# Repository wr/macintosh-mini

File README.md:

<h1 align="center"> Macintosh Mini</h1>

<p align="center">
  <strong>Turn a Maclock alarm clock into a working Mac with a Raspberry Pi</strong>
</p>

<p align="center">
  <a href="https://wells.ee/projects/macintosh-mini/?ref=gh-macintosh-mini">Build guide</a> ⬪
  <a href="#step-2-install-the-software">Install the software</a> ⬪
  <a href="https://shop.wells.ee/products/macintosh-mini/?ref=gh-macintosh-mini">Buy a kit</a> ⬪
  <a href="#donate">Donate</a>
</p>

<p align="center">
  
  <br />
  <a href="https://www.youtube.com/watch?v=zAbAf5-H5Yo">⏵ Watch the full build on YouTube</a>
</p>

---

## What is it?

A [Maclock](https://www.aliexpress.us/w/wholesale-maclock.html) is a cheap alarm clock built into a shockingly accurate miniature Macintosh shell. This project guts one and rebuilds it around a Raspberry Pi Zero running a 68k or PowerPC emulator, so the tiny Mac actually boots System 7, plays the startup chime, and runs vintage software. Buttons, brightness, sound, Wi-Fi, Bluetooth, and battery all work.

## Step 1: Build or buy one

The [build guide](https://wells.ee/projects/macintosh-mini/?ref=gh-macintosh-mini), on my site, covers everything from opening the clock to the first boot: parts, assembly, software, and troubleshooting.

You can [buy a DIY kit or a finished build](https://shop.wells.ee/products/macintosh-mini/?ref=gh-macintosh-mini) from my maker shop. Faster than shipping from China, and your purchase supports the continued development of this project.

## Step 2: Install the software

**You will need:**
- A Mac ROM file (`064DC91D` is a common one to search for)
- A Mac OS disk image with System 7.0 to 8.5. The [BlueSCSI image library](https://bluescsi.com/docs/BlueSCSI-Images) has ready-made ones, or skip it: the installer offers [our Mac OS 8.1 disk](https://archive.org/details/macos-8.1-basilisk-ii)

**Prepare the MicroSD card**
1. Flash **Raspberry Pi OS Lite (64-bit)** to a microSD card with [Raspberry Pi Imager](https://www.raspberrypi.com/software/). Set your Wi-Fi network and turn on SSH in its settings.
2. Rename your Mac ROM file to `ROM`, and copy it and your disk image, if you have one, to the Pi's home folder:

   ```bash
   scp ROM yourdisk.hda <user>@<pi_ip>:~/
   ```

3. SSH into the Pi and run the install script. It asks a few questions, like which startup chime to play, then does the rest:

   ```bash
   curl -fsSL https://raw.githubusercontent.com/wr/macintosh-mini/main/setup.sh | bash
   ```

The Pi automatically restarts into Mac OS when it's done.

You can run the same command again to install future updates.

* * *

_Optional:_ If you want to skip the automatic script and install everything yourself, or see exactly what the script changes:

- [Set up the Pi](maclock-build/): display, audio, brightness dial and buttons.
-  [Install the emulator](emulators/): Basilisk II or SheepShaver.

## Getting help

Ask in the help forum on [Wells Workshop on Discord](https://discord.gg/gACNgfyB7k), where other builders can help too. Found a bug or want a feature? Open a [GitHub issue](https://github.com/wr/macintosh-mini/issues).

## Credits

Startup chimes and crash sounds are mirrored from D. Schaub's Apple Sounds collection at <https://froods.ca/~dschaub/sound.html>. All sounds are © Apple, Inc.

## Donate

While this project is free and open source, donations are deeply appreciated, and make ongoing development and support possible.
[Donate now](https://www.buymeacoffee.com/wellsworkshop)

## License

Copyright © 2026 Wells Riley.

- **Hardware** (the boards, the bezel and the USB port jig): [CERN-OHL-S-2.0](./LICENSES/CERN-OHL-S-2.0.txt)
- **Software** ([`setup.sh`](./setup.sh) and [`maclock-build/`](./maclock-build/)): [GPL-3.0-or-later](./LICENSES/GPL-3.0-or-later.txt)
- **Everything else** (docs, drawings, photos): [CC BY-SA 4.0](./LICENSES/CC-BY-SA-4.0.txt)

The [Mac chimes](./emulators/chimes/) are Apple's and the display overlay is Waveshare's; neither is covered. [`REUSE.toml`](./REUSE.toml) maps every file.

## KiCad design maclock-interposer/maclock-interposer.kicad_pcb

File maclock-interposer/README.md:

# Macintosh Mini GPIO interposer

A 64.6 × 27.4 mm, 2-layer, 0.8 mm thick KiCad 10 board that sits between the Raspberry Pi (a Zero 2 W or a 3 A+) and the Waveshare 2.8" DPI display. Order it fully assembled — no soldering, and no bent, cut, or desoldered pins on the Pi.

Current revision: 2027.01, for the rev 2027.01 [main board](../maclock-pcb/). **It hasn't been built or tested yet, and the Pi software for it isn't written.** The two revisions don't mix, because their link pins differ: with a rev 2026.11 main board, use the 2026.11 interposer at commit [`e557f70`](https://github.com/wr/macintosh-mini/tree/e557f70d8a1d978d0e488f638d03199df252ab32/maclock-interposer).

An SMD pin header on top plugs into the display and an SMD socket underneath plugs onto the Pi. The socket sits 6 mm lower than the header, so a Pi 3 A+ (65 × 56 mm) clears the handle at the top of the Maclock's rear shell. 35 pins run from one to the other, one via each. Header pins 13, 19, 23, 35 and 37 connect to the Pi side **only** and never reach the display. Four of them, plus 5V and GND, come out on a straight 1×8 female socket (J2) on the screen side at the GPIO 21 end. J2 plugs straight onto the main board's `Link` header, pin 1 onto pin 1, so its pin 1 (SDA) sits at the end away from GPIO 21. A straight 8-way male-to-female Dupont cable works too. Pin 37 (GPIO 26) is unused.

The display uses the Pi's hardware I²C pins for its sync signals, so the Pi reaches the main board's input chip and battery gauge over a software I²C bus on GPIO 10 and 11. Three resistors on the Pi side complete the link. R1 and R2 pull SDA and SCL up to the Pi's 3.3 V. R3 pulls up INT, which the main board's input chip only ever pulls low. The main board has none of these, because the ESP32-P4 build brings its own. The Pi's own pull-up or pull-down on GPIO 10, 11 and 27 should be switched off in software.

The board is drawn the way it sits in the Maclock: Pi mounted upside-down, seen from the screen. Order it **0.8 mm thick**, with **red solder mask and white silkscreen** like the 2027.01 main board, so it can't be paired with a blue 2026.11 board by mistake. The screen side is inverted (silk is the background; the lettering, the open-hardware logo and the character are bare mask). Branding is on the Pi side, and J2's pin labels are on both sides.

| J2 pin | Silk | Net   | Pi header pin | GPIO |
| ------ | ---- | ----- | ------------- | ---- |
| 1      | SDA  | SDA   | 19            | 10   |
| 2      | SCL  | SCL   | 23            | 11   |
| 3      | GND  | GND   | all GNDs      | —    |
| 4      | 5V   | 5V    | 2, 4          | —    |
| 5      | 5V   | 5V    | 2, 4          | —    |
| 6      | GND  | GND   | all GNDs      | —    |
| 7      | INT  | INT   | 13            | 27   |
| 8      | AUD  | AUDIO | 35            | 19   |

## Bill of materials

| Ref | Qty | Part                                                                  | LCSC                                                                  | Notes                                             |
| --- | --- | --------------------------------------------------------------------- | --------------------------------------------------------------------- | ------------------------------------------------- |
| J1  | 1   | 2×20 female socket, 2.54 mm, SMD, 7.1 mm, two locating pegs — Liansheng `FH-00148` | [`C2685092`](https://www.lcsc.com/product-detail/C2685092.html) | **Bottom** side, plugs onto the Pi. LCSC had 3,698 in stock on 2026-11-28 |
| J3  | 1   | 2×20 pin header, 2.54 mm, SMD — Hanbo `HB-PH9-254220PB2GOP`            | [`C6332245`](https://www.lcsc.com/product-detail/C6332245.html)       | Top side, plugs into the display                  |
| J2  | 1   | 1×8 female header (socket), 2.54 mm, 7.1 mm, THT — XFCN `PM254V-11-08-H71-U` | [`C55218707`](https://www.lcsc.com/product-detail/C55218707.html) | Top (screen) side. LCSC had 190 in stock on 2026-11-27 |
| R1, R2 | 2 | 2.2 kΩ ±1% 0402 — UNI-ROYAL `0402WGF2201TCE`                          | [`C25879`](https://www.lcsc.com/product-detail/C25879.html)           | Bottom side. I²C pull-ups on SDA and SCL          |
| R3  | 1   | 10 kΩ ±1% 0402 — UNI-ROYAL `0402WGF1002TCE`                            | [`C25744`](https://www.lcsc.com/product-detail/C25744.html)           | Bottom side. Pull-up on INT                       |

Both sides carry parts, so order two-sided assembly. J1's locating pegs are 1.4 mm long, so on a 0.8 mm board they stick out of the screen side beside J3: ask for the screen side (J3) to be pasted and placed first. J1's footprint (in `maclock-interposer.pretty`) follows its datasheet: 2.3 × 1.02 mm pads and two 1.2 mm holes for its pegs. J3 still uses KiCad's generic land (3.15 × 1.0 mm pads, ±2.52 mm from the centreline); Hanbo's drawing suggests 3.2 × 1.02 mm pads with their outer ends 8.6 mm apart, so check J3 against it before ordering.

## Use

Stack Pi → interposer → display, with the side marked `THIS SIDE FACING SCREEN` toward the display. Plug J2 straight onto the main board's `Link` header, `SDA` (J2's square pad) onto `SDA`. Each side's labels then line up with the other's.

The interposer adds about 10.4 mm between the Pi and the display (7.1 mm socket + 0.8 mm PCB + 2.54 mm header base). The Pi sits 6 mm lower than the display's socket, so a Pi 3 A+ ends about 3 mm above the display's top edge and a Zero 2 W about 23 mm below it. The board reaches 4.2 mm past the Pi's header edge. The Pi's two mounting holes on its header side line up with H1 and H2: fix them with M2.5 screws and spacers 9.6 mm long (the Pi's 2.5 mm header base plus J1). That isn't a stock length: 10 mm spacers work but leave the Pi 0.4 mm short of fully seated. J2 stands 7.1 mm off the screen side, and the Dupont plug in it points toward the display — check both against your case and the display board before ordering.

## License

CERN-OHL-S-2.0, same as the [main board](../maclock-pcb/README.md#license) — see [`LICENSE`](./LICENSE).

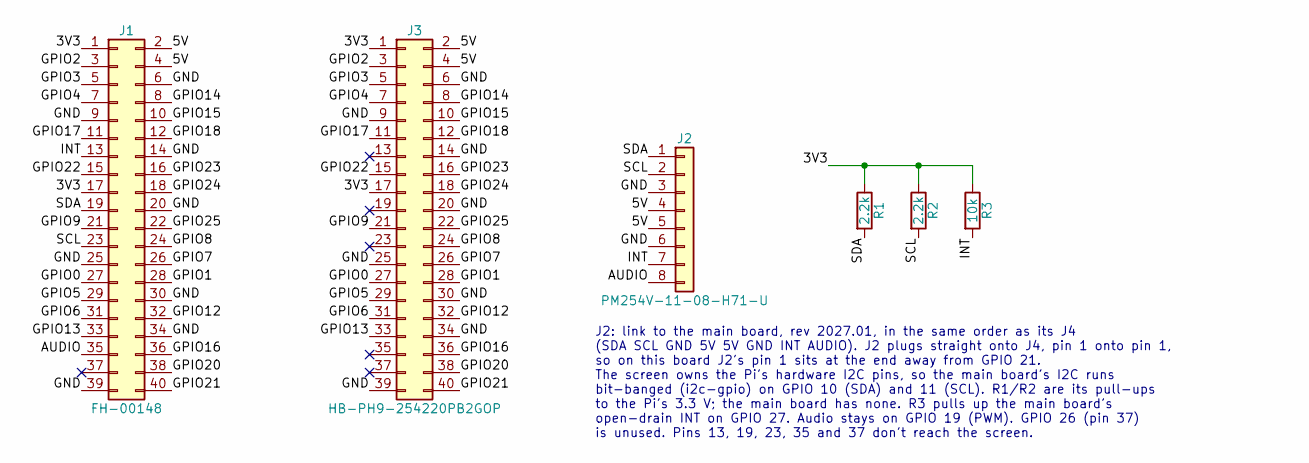
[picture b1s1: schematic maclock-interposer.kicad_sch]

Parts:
J1: FH-00148; PinSocket_2x20_P2.54mm_Vertical_SMD_Liansheng_FH-00148; MPN FH-00148; LCSC C2685092
J2: PM254V-11-08-H71-U; PinSocket_1x08_P2.54mm_Vertical; MPN PM254V-11-08-H71-U; LCSC C55218707
J3: HB-PH9-254220PB2GOP; PinHeader_2x20_P2.54mm_Vertical_SMD; MPN HB-PH9-254220PB2GOP; LCSC C6332245
R1, R2: 2.2k; R_0402_1005Metric_Pad0.72x0.64mm_HandSolder; MPN 0402WGF2201TCE; LCSC C25879
R3: 10k; R_0402_1005Metric_Pad0.72x0.64mm_HandSolder; MPN 0402WGF1002TCE; LCSC C25744

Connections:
/3V3: J1.1, J1.17, J3.1, J3.17, R1.1, R2.1, R3.1
/5V: J1.2, J1.4, J2.4, J2.5, J3.2, J3.4
/AUDIO: J1.35, J2.8
/GND: J1.6, J1.9, J1.14, J1.20, J1.25, J1.30, J1.34, J1.39, J2.3, J2.6, J3.6, J3.9, J3.14, J3.20, J3.25, J3.30, J3.34, J3.39
/GPIO0: J1.27, J3.27
/GPIO1: J1.28, J3.28
/GPIO2: J1.3, J3.3
/GPIO3: J1.5, J3.5
/GPIO4: J1.7, J3.7
/GPIO5: J1.29, J3.29
/GPIO6: J1.31, J3.31
/GPIO7: J1.26, J3.26
/GPIO8: J1.24, J3.24
/GPIO9: J1.21, J3.21
/GPIO12: J1.32, J3.32
/GPIO13: J1.33, J3.33
/GPIO14: J1.8, J3.8
/GPIO15: J1.10, J3.10
/GPIO16: J1.36, J3.36
/GPIO17: J1.11, J3.11
/GPIO18: J1.12, J3.12
/GPIO20: J1.38, J3.38
/GPIO21: J1.40, J3.40
/GPIO22: J1.15, J3.15
/GPIO23: J1.16, J3.16
/GPIO24: J1.18, J3.18
/GPIO25: J1.22, J3.22
/INT: J1.13, J2.7, R3.2
/SCL: J1.23, J2.2, R2.2
/SDA: J1.19, J2.1, R1.2

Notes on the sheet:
J2: link to the main board, rev 2027.01, in the same order as its J4 (SDA SCL GND 5V 5V GND INT AUDIO). J2 plugs straight onto J4, pin 1 onto pin 1, so on this board J2's pin 1 sits at the end away from GPIO 21. The screen owns the Pi's hardware I2C pins, so the main board's I2C runs bit-banged (i2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

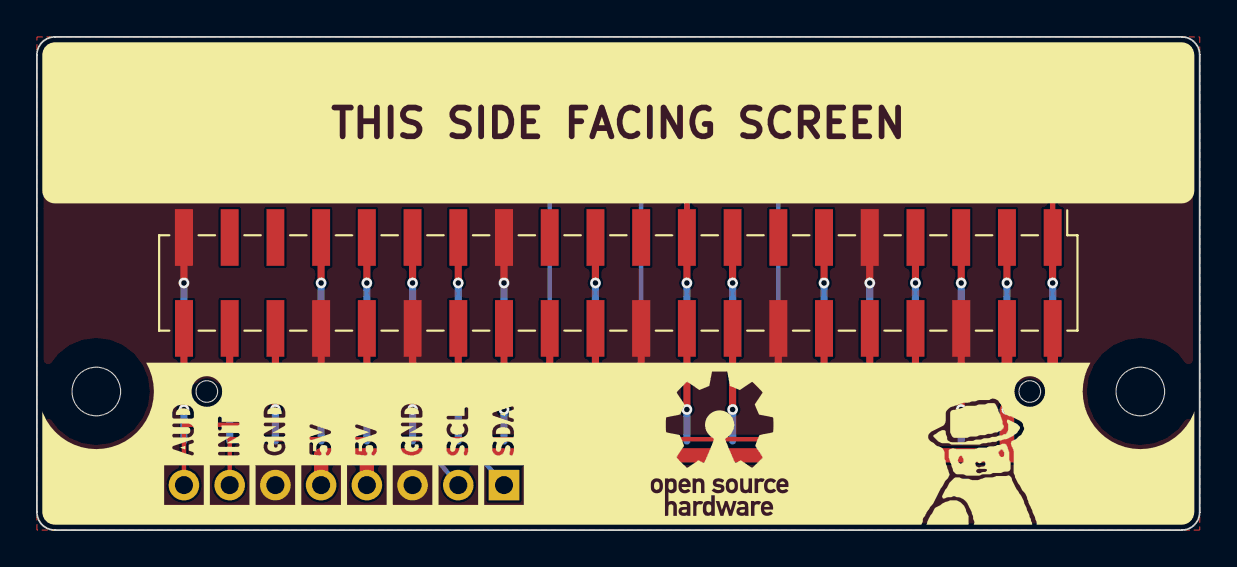
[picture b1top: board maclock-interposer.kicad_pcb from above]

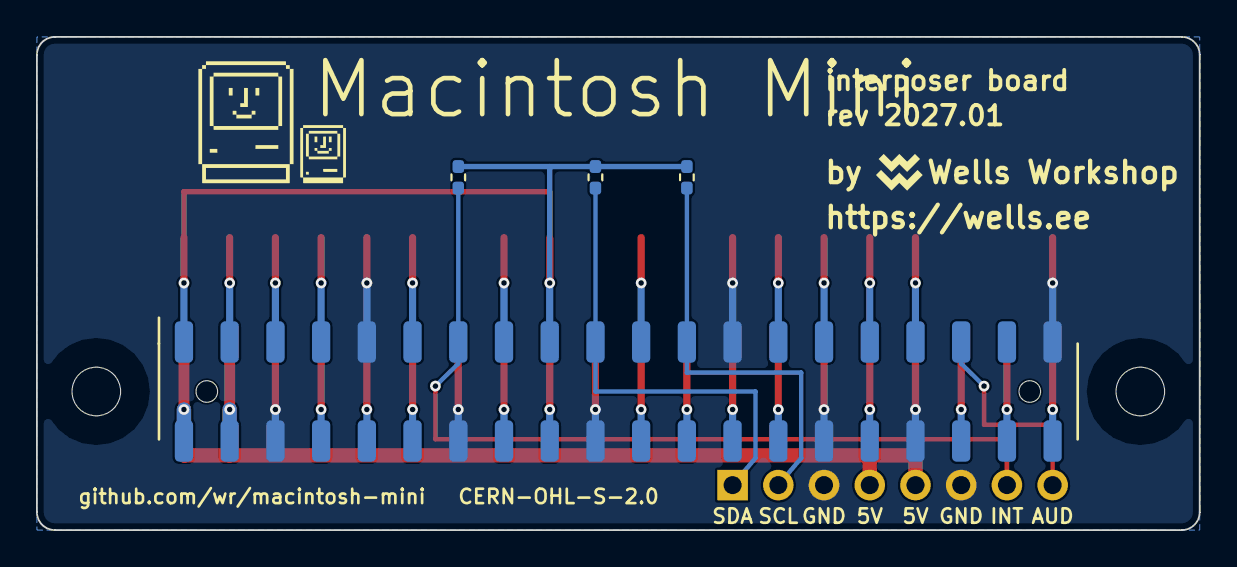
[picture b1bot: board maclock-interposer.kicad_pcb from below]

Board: 2 copper layers, 64.6 x 27.4 mm, 8 parts (4 on the bottom side), 30 nets.

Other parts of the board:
H1, H2: MountingHole_2.7mm_M2.5

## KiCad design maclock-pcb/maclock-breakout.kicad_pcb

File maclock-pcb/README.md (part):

# Macintosh Mini breakout PCB

KiCad 10 project for the board behind the Mac-shaped clock's screen. It holds the clock's front-panel parts (rotary encoder, two pushbuttons, speaker, power switch and battery harness) and links them to the computer through an 8-pin header. The same board serves the Raspberry Pi and ESP32-P4 builds. It also carries the PAM8302A speaker amplifier, a 5 V supply for the computer, a low-battery cutoff, an input chip that reads the dial and buttons, and a battery gauge (see [Design notes](#design-notes)).

Current revision: 2027.01. **It hasn't been built or tested yet, and the software that goes with it isn't written.** Its Pi interposer is the rev 2027.01 board in [`maclock-interposer/`](../maclock-interposer/). To build a working Mini today, use rev 2026.11: its files are at commit [`ea41efe`](https://github.com/wr/macintosh-mini/tree/ea41efe2434ef0056f3ba3236e3c8bb0ac9fd945/maclock-pcb), the PCBway project below builds it, and [step 2 of the build guide](https://wells.ee/projects/macintosh-mini/#2-connect-the-pi-to-the-screen-and-the-board) wires it to the Pi. Rev 2026.09 boards, the first ones that shipped, work but whine faintly with the Pi running.

For the case-side parts you'll print, see the [3D-printed screen bezel](../maclock-screen-bezel/).

Order rev 2027.01 with **red solder mask and white silkscreen**, so it can't be mixed up with the blue 2026.11 boards. The [PCBway project](https://www.pcbway.com/project/shareproject/W654223ASS41_Untitled_kicad_pcb_95cca7e3.html) builds rev 2026.11. You can [use my referral code](https://pcbway.com/g/AsfKU9) to get $5 off your order, if you want.

## Bill of materials

To populate one board. Every part except ENC1 has an LCSC part number, so PCBway can assemble the board with ENC1 left off; it is out of the BOM and placement files, so fit it yourself afterwards. Only the link header is through-hole. The DigiKey column is for hand assembly: where DigiKey does not carry the LCSC part, a drop-in equivalent is named.

| Ref | Qty | Part | DigiKey (hand assembly) | Notes |
| --- | --- | --- | --- | --- |
| C1 | 1 | 10 nF X7R 0603 — FH `0603B103K500NT` (LCSC [`C57112`](https://www.lcsc.com/product-detail/C57112.html)) | [`1276-1009-1-ND`](https://www.digikey.com/en/products/result?keywords=1276-1009-1-ND) Samsung `CL10B103KB8NNNC` | Audio low-pass with R3 |
| C2, C3 | 2 | 220 nF X7R 0603 — Samsung `CL10B224KA8NNNC` (LCSC [`C21120`](https://www.lcsc.com/product-detail/C21120.html)) | [`1276-1111-1-ND`](https://www.digikey.com/en/products/result?keywords=1276-1111-1-ND) | Amp input coupling (IN+ and IN−) |
| C4, C8, C10 | 3 | 1 µF X5R 0603 — Samsung `CL10A105KB8NNNC` (LCSC [`C15849`](https://www.lcsc.com/product-detail/C15849.html)) | [`478-KGM15BR51E105KTCT-ND`](https://www.digikey.com/en/products/result?keywords=478-KGM15BR51E105KTCT-ND) KYOCERA AVX `06033D105KAT2A` (25 V) | Amp supply decoupling (C4); U3 input (C8); U3 output and U2 supply (C10) |
| C5, C12 | 2 | 10 µF X5R 0805 — Samsung `CL21A106KAYNNNE` (LCSC [`C15850`](https://www.lcsc.com/product-detail/C15850.html)) | [`490-16824-1-ND`](https://www.digikey.com/en/products/result?keywords=490-16824-1-ND) Murata `GRM21BR61E106KA73K` | Amp bulk decoupling (C5); boost input, with C11 (C12) |
| C6 | 0 | 470 pF C0G 0402 — Samsung `CL05C471JB5NNNC` (LCSC [`C307449`](https://www.lcsc.com/product-detail/C307449.html)) | [`1276-1117-1-ND`](https://www.digikey.com/en/products/result?keywords=1276-1117-1-ND) | **Not fitted**, left off the BOM and placement file. Optional second filter pole across the amp inputs, between R4 and R5 (see [Design notes](#design-notes)) |
| C11, C13–C16, C19 | 6 | 22 µF X5R 25 V 0805 — Samsung `CL21A226MAQNNNE` (LCSC [`C45783`](https://www.lcsc.com/product-detail/C45783.html)) | [`445-9112-1-ND`](https://www.digikey.com/en/products/result?keywords=445-9112-1-ND) TDK `C2012X5R1E226M125AC` | Boost input (C11) and output (C13, C14); the computer's 5 V after the one-way switch (C15); the cutoff's delay (C16, C19) |
| C17, C18, C20, C21 | 4 | 100 nF X7R 0402 — Samsung `CL05B104KO5NNNC` (LCSC [`C1525`](https://www.lcsc.com/product-detail/C1525.html)) | [`1276-1001-1-ND`](https://www.digikey.com/en/products/result?keywords=1276-1001-1-ND) | Supply decoupling for U7 (C17) and U6 (C18); noise filter on the cutoff's latch (C20); delay on the amp's shutdown pin (C21) |
| C22 | 0 | 220 pF C0G 0402 — Samsung `CL05C221JB5NNNC` (LCSC [`C307445`](https://www.lcsc.com/product-detail/C307445.html)) | [search `CL05C221JB5NNNC`](https://www.digikey.com/en/products/result?keywords=CL05C221JB5NNNC) | **Not fitted**, left off the BOM and placement file. Room for a feedforward capacitor across R7 (see [Design notes](#design-notes)) |
| D1 | 1 | Schottky diode, SOD-323 — Diodes `BAT54WS-7-F` (LCSC [`C124205`](https://www.lcsc.com/product-detail/C124205.html)) | [`BAT54WS-FDICT-ND`](https://www.digikey.com/en/products/result?keywords=BAT54WS-FDICT-ND) | Clamps the boost's enable line when the cutoff's capacitors discharge at switch-off |
| ENC1 | 1 | Rotary encoder, HUANO 4.5 mm mouse-wheel type, laid on its back with the hex bore up — sold as MECCANIXITY on [Amazon](https://www.amazon.com/dp/B0C13ZZVT5) (10-pack) and on [AliExpress](https://www.aliexpress.us/item/3256805576298875.html) (choose 4.5MM); not stocked at LCSC, DigiKey or Mouser | — (no equivalent at DigiKey) | The dial. Body 9.54 × 8.34 × 4.15 mm, 1.74 mm hex bore, 2.5 mm pin pitch. **Fitted by hand**, left out of the BOM and placement file: lay it on its black back over the bore with the marked metal face up and the pins north, bend the pins down onto their pads and solder, and do the same with the two clip legs on the MP pads for strength. Seen from the marked face with the pins down, the common pin is on the left, as on TT's and HOAUC's mouse-wheel encoders, so face up it lands on C, the east pad |
| J1 | 1 | Molex PicoBlade 1×2, 1.25 mm, SMD top entry — `53398-0271` (LCSC [`C122410`](https://www.lcsc.com/product-detail/C122410.html)) | [`WM7606CT-ND`](https://www.digikey.com/en/products/result?keywords=WM7606CT-ND) | **Power switch**, in series with the battery supply; silkscreened "Switch". Takes the Maclock's 2-wire switch plug |
| J2 | 1 | Molex PicoBlade 1×4, 1.25 mm, SMD top entry — `53398-0471` (LCSC [`C17617036`](https://www.lcsc.com/product-detail/C17617036.html)) | [`WM7608CT-ND`](https://www.digikey.com/en/products/result?keywords=WM7608CT-ND) | **Power input**, silkscreened "Power". Takes the Maclock's 4-wire plug: pin 1 (silk `+`) = battery supply, about 4 V (the clock's charging board passes the cell through, it does not boost it), pin 2 (silk `-`) = GND, pins 3–4 unused |
| J3 | 1 | Molex PicoBlade 1×2, 1.25 mm, SMD top entry — `53398-0271` (LCSC [`C122410`](https://www.lcsc.com/product-detail/C122410.html)) | [`WM7606CT-ND`](https://www.digikey.com/en/products/result?keywords=WM7606CT-ND) | **Speaker**, silkscreened "Spkr". Same part as J1; polarity does not matter |
| J4 | 1 | 1×8 male pin header, 2.54 mm — XFCN `PZ254V-11-08P` (LCSC [`C492407`](https://www.lcsc.com/product-detail/C492407.html)) | [`35-PRPC008SAAN-RC-ND`](https://www.digikey.com/en/products/result?keywords=35-PRPC008SAAN-RC-ND) Sullins `PRPC008SAAN-RC` | Through-hole, silkscreened "Link", with each pin labelled. The link to the computer: 1 SDA, 2 SCL, 3 GND, 4 5V, 5 5V, 6 GND, 7 INT, 8 AUDIO |
| L1 | 1 | 1 µH power inductor, 3.2 × 2.5 mm — Murata `DFE322520F-1R0M=P2` (LCSC [`C5623631`](https://www.lcsc.com/product-detail/C5623631.html)) | [`490-DFE322520F-1R0M=P2CT-ND`](https://www.digikey.com/en/products/result?keywords=490-DFE322520F-1R0M%3DP2CT-ND) | The boost's inductor |
| Q1 | 1 | P-channel MOSFET, SOT-23 — Alpha & Omega `AO3401A` (LCSC [`C15127`](https://www.lcsc.com/product-detail/C15127.html)) | [`785-1001-1-ND`](https://www.digikey.com/en/products/result?keywords=785-1001-1-ND) | One-way switch on the computer's 5 V, with Q2 |
| Q2 | 1 | Dual PNP, SOT-363 — JSCJ `MMDT3906` (LCSC [`C20534`](https://www.lcsc.com/product-detail/C20534.html)) | [`MMDT3906-FDICT-ND`](https://www.digikey.com/en/products/result?keywords=MMDT3906-FDICT-ND) Diodes `MMDT3906-7-F` | Drives Q1 |
| Q3 | 1 | NPN + PNP pair, SOT-363 — onsemi `MBT3946DW1T1G` (LCSC [`C28272`](https://www.lcsc.com/product-detail/C28272.html)) | [`MBT3946DW1T1GOSCT-ND`](https://www.digikey.com/en/products/result?keywords=MBT3946DW1T1GOSCT-ND) | The cutoff's latch |
| R3 | 1 | 1 kΩ ±1% 0402 — UNI-ROYAL `0402WGF1001TCE` (LCSC [`C11702`](https://www.lcsc.com/product-detail/C11702.html)) | [`311-1.00KLRCT-ND`](https://www.digikey.com/en/products/result?keywords=311-1.00KLRCT-ND) Yageo `RC0402FR-071KL` | With C1, the 16 kHz low-pass on the rebuilt PWM audio |
| R4, R5 | 2 | 47 kΩ ±1% 0402 — UNI-ROYAL `0402WGF4702TCE` (LCSC [`C25792`](https://www.lcsc.com/product-detail/C25792.html)) | [`311-47.0KLRCT-ND`](https://www.digikey.com/en/products/result?keywords=311-47.0KLRCT-ND) Yageo `RC0402FR-0747KL` | Amp input resistors, set the gain to about 8 dB |
| R6, R8, R12–R18 | 9 | 100 kΩ ±1% 0402 — UNI-ROYAL `0402WGF1003TCE` (LCSC [`C25741`](https://www.lcsc.com/product-detail/C25741.html)) | [`311-100KLRCT-ND`](https://www.digikey.com/en/products/result?keywords=311-100KLRCT-ND) Yageo `RC0402FR-07100KL` | Divider on the amp's shutdown pin (R6, R18); boost output setting, with R7 (R8); the cutoff and its latch (R12–R14, R16, R17); holds the link's AUDIO pin low when nothing drives it (R15) |
| R7 | 1 | 750 kΩ ±1% 0402 — UNI-ROYAL `0402WGF7503TCE` (LCSC [`C122545`](https://www.lcsc.com/product-detail/C122545.html)) | [`YAG3228CT-ND`](https://www.digikey.com/en/products/result?keywords=YAG3228CT-ND) Yageo `RC0402FR-07750KL` | Sets the boost to 5.06 V, with R8 |
| R9 | 1 | 10 kΩ ±1% 0402 — UNI-ROYAL `0402WGF1002TCE` (LCSC [`C25744`](https://www.lcsc.com/product-detail/C25744.html)) | [`311-10.0KLRCT-ND`](https://www.digikey.com/en/products/result?keywords=311-10.0KLRCT-ND) Yageo `RC0402FR-0710KL` | One-way switch |
| R10 | 1 | 51 kΩ ±1% 0402 — UNI-ROYAL `0402WGF5102TCE` (LCSC [`C25794`](https://www.lcsc.com/product-detail/C25794.html)) | [`311-51.0KLRCT-ND`](https://www.digikey.com/en/products/result?keywords=311-51.0KLRCT-ND) Yageo `RC0402FR-0751KL` | One-way switch |
| SW1, SW2 | 2 | BZCN `TSB001A3518A` side-press SMD tactile, 7.7 × 3.55 mm, 180 gf (LCSC [`C2888448`](https://www.lcsc.com/product-detail/C2888448.html)) | [`2223-TS32-7-35-BK-B-160-RA-SMT-TRCT-ND`](https://www.digikey.com/en/products/result?keywords=2223-TS32-7-35-BK-B-160-RA-SMT-TRCT-ND) Same Sky `TS32-7-35-BK-B-160-RA-SMT-TR`: same land (its pegs, shell pads and 4.2 mm signal pitch match; the signal pads sit 0.15 mm closer to the pegs), but 160 gf, and the button sits about 0.15 mm lower and 0.2 mm further out. Not yet tried in the case | The two front buttons |
| U1 | 1 | PAM8302A 2.5 W class-D mono amp, MSOP-8 — Diodes `PAM8302AASCR` (LCSC [`C113367`](https://www.lcsc.com/product-detail/C113367.html)) | [`PAM8302AASCRDICT-ND`](https://www.digikey.com/en/products/result?keywords=PAM8302AASCRDICT-ND) | Bottom side |
| U2 | 1 | Single Schmitt-trigger buffer, SOT-753 (the SOT-23-5 land) — Nexperia `74LVC1G17GV,125` (LCSC [`C6076`](https://www.lcsc.com/product-detail/C6076.html)) | [`1727-6070-1-ND`](https://www.digikey.com/en/products/result?keywords=1727-6070-1-ND) | Rebuilds the Pi's PWM audio from U3's 3.0 V |
| U3 | 1 | 3.0 V low-noise LDO, SOT-23-5 — TI `TPS7A2030PDBVR` (LCSC [`C963429`](https://www.lcsc.com/product-detail/C963429.html)) | [`296-TPS7A2030PDBVRCT-ND`](https://www.digikey.com/en/products/result?keywords=296-TPS7A2030PDBVRCT-ND) | Quiet 3.0 V for U2 |
| U4 | 1 | 5 V boost converter, SOT-563 — TI `TPS61023DRLR` (LCSC [`C919459`](https://www.lcsc.com/product-detail/C919459.html)) | [`296-TPS61023DRLRCT-ND`](https://www.digikey.com/en/products/result?keywords=296-TPS61023DRLRCT-ND) | Makes the computer's 5 V from the battery |
| U5 | 1 | 3.08 V reset supervisor, SOT-23 — Analog Devices `MAX809TEUR+T` (LCSC [`C16711`](https://www.lcsc.com/product-detail/C16711.html)) | [`MAX809TEUR+TCT-ND`](https://www.digikey.com/en/products/result?keywords=MAX809TEUR%2BTCT-ND) | Watches the battery for the low-battery cutoff |
| U6 | 1 | Battery gauge, TDFN-8 2 × 2 mm — Analog Devices `MAX17048G+T10` (LCSC [`C2682616`](https://www.lcsc.com/product-detail/C2682616.html)) | [`MAX17048G+T10CT-ND`](https://www.digikey.com/en/products/result?keywords=MAX17048G%2BT10CT-ND) | I²C address 0x36 |
| U7 | 1 | 8-bit I²C input/output chip, TSSOP-16 — TI `TCA9554PWR` (LCSC [`C477924`](https://www.lcsc.com/product-detail/C477924.html)) | [`296-30135-1-ND`](https://www.digikey.com/en/products/result?keywords=296-30135-1-ND) | Reads the dial and buttons; I²C address 0x20 |
| — | 1 | Small speaker, 8 Ω, 1 W, 28–40 mm, PicoBlade 1.25 mm 2-pin plug (often sold as "JST 1.25"), e.g. [Adafruit 3923](https://www.adafruit.com/product/3923) | — | Whatever fits behind the Maclock grille |

The schematic carries the same data in each symbol's `Manufacturer`, `MPN` and `LCSC` fields. ENC1 is left out of exported BOMs, so its source is only in its symbol's `Supplier` and `Supplier Link` fields.

## Design notes

**Power.** J2 brings in the clock's battery, about 4 V at full charge, and the power switch on J1 is in series with it. After the switch (net `+BATT`), the battery feeds the amp and its regulator, the input chip and the cutoff, and U4, a boost converter that makes 5.06 V for the computer (set by R7/R8). The 5 V leaves through Q1, a one-way switch driven by Q2, so a Pi powered from its own USB port can't push current back into the battery. The boost, its capacitors and the link's two GND pins have their own ground copper (net `GND_PWR`), joined to the board ground only at the net tie NT1 by J2, so the computer's return current never flows through the amp's ground. On the rev 2026.09 boards it did, and the amp shared the Pi's supply copper, which put a faint whine in the speaker: a 1 kHz comb from the backlight PWM, plus drifting tones from the emulator's load. NT1 is copper only, so it is not in the BOM. The amp takes its supply straight from J1, ahead of the boost, and its 1 µF decoupling capacitor sits right against its supply and ground pins.

**Low-battery cutoff.** U5 watches the battery. When it falls below 3.08 V, U5 pulls the boost's enable line down; after about 2.5 s (set by C16/C19) the Q3 latch holds it down, so the computer and the amp stay off until the power switch is turned off and back on. The switch has to stay off for several seconds (about 10 s by calculation) while C16/C19 drain, or the latch catches again at once. The delay keeps U5's reset pulse at power-up (up to 560 ms) from tripping the latch. D1 clamps the enable line as those capacitors discharge at switch-off. The timings are calculated and haven't been measured on a board yet.

**5 V stability.** C22 is a spare pad across R7, not fitted. TI recommends a feedforward capacitor once the boost's output capacitance passes 40 µF. This board has roughly 27 µF at 5 V (the 22 µF parts lose more than half their value at that voltage), plus whatever the Pi or P4 adds. Fit 220 pF there only if the 5 V rings or oscillates on a first board.

**Audio input.** The Pi's audio is PWM on GPIO 19, on the link's AUDIO pin, switching between the Pi's own 3.3 V and ground, so it carries whatever noise the Pi's supply and ground do. U2 rebuilds it from U3, a separate low-noise 3.0 V regulator (net `+3V0`), so only the timing of the Pi's signal reaches the amp. U3 runs from the clock's battery, which is about 4 V at full charge and falls as it drains, so it is a 3.0 V part rather than 3.3 V: that keeps it far enough above its dropout to keep filtering as the battery runs down. R3/C1 then low-pass it at 16 kHz. R15 holds AUDIO low when nothing drives it, as in the ESP32-P4 build, which plays sound through its own board.

**Amplifier.** The filtered signal goes C2 → R4 → PAM8302A IN+, with IN− terminated through the matching R5/C3 pair. R4 adds to the chip's internal 10 kΩ input resistor, which brings its fixed 23.5 dB gain down to about 8 dB; fine volume is a software setting, and `setup.sh` leaves 4 dB of headroom so the startup chime's peaks don't clip. The shutdown pin sits at about 2.5 V, divided by R6/R18 from the boost's output, so the amp is on whenever the computer is powered and the cutoff turns it off too. It comes from the output rather than the enable line so that nothing the amp's pin draws can pull on the cutoff's latch: the datasheet doesn't say whether the pin has a pull-down inside. C21 holds the pin low for a few milliseconds after the boost starts, which the datasheet asks for to avoid a pop at switch-on.

C6 is a spare pad, not fitted. R3/C1 is a single pole, which takes only about 24 dB off the Pi's PWM noise near the amp's own 200–300 kHz switching frequency, where a class-D amp can fold it back into the audio band as hiss or a faint whistle. A 470 pF across IN+ and IN− adds a second pole at about 20 kHz (with R4/R5 and the chip's internal 10 kΩ), for roughly 46 dB there, at the cost of about 1 dB at 10 kHz. The rev 2026.09 boards have the same single pole and none of their measured noise came from it, so solder C6 on only if a board hisses or whistles with the amp warm.

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
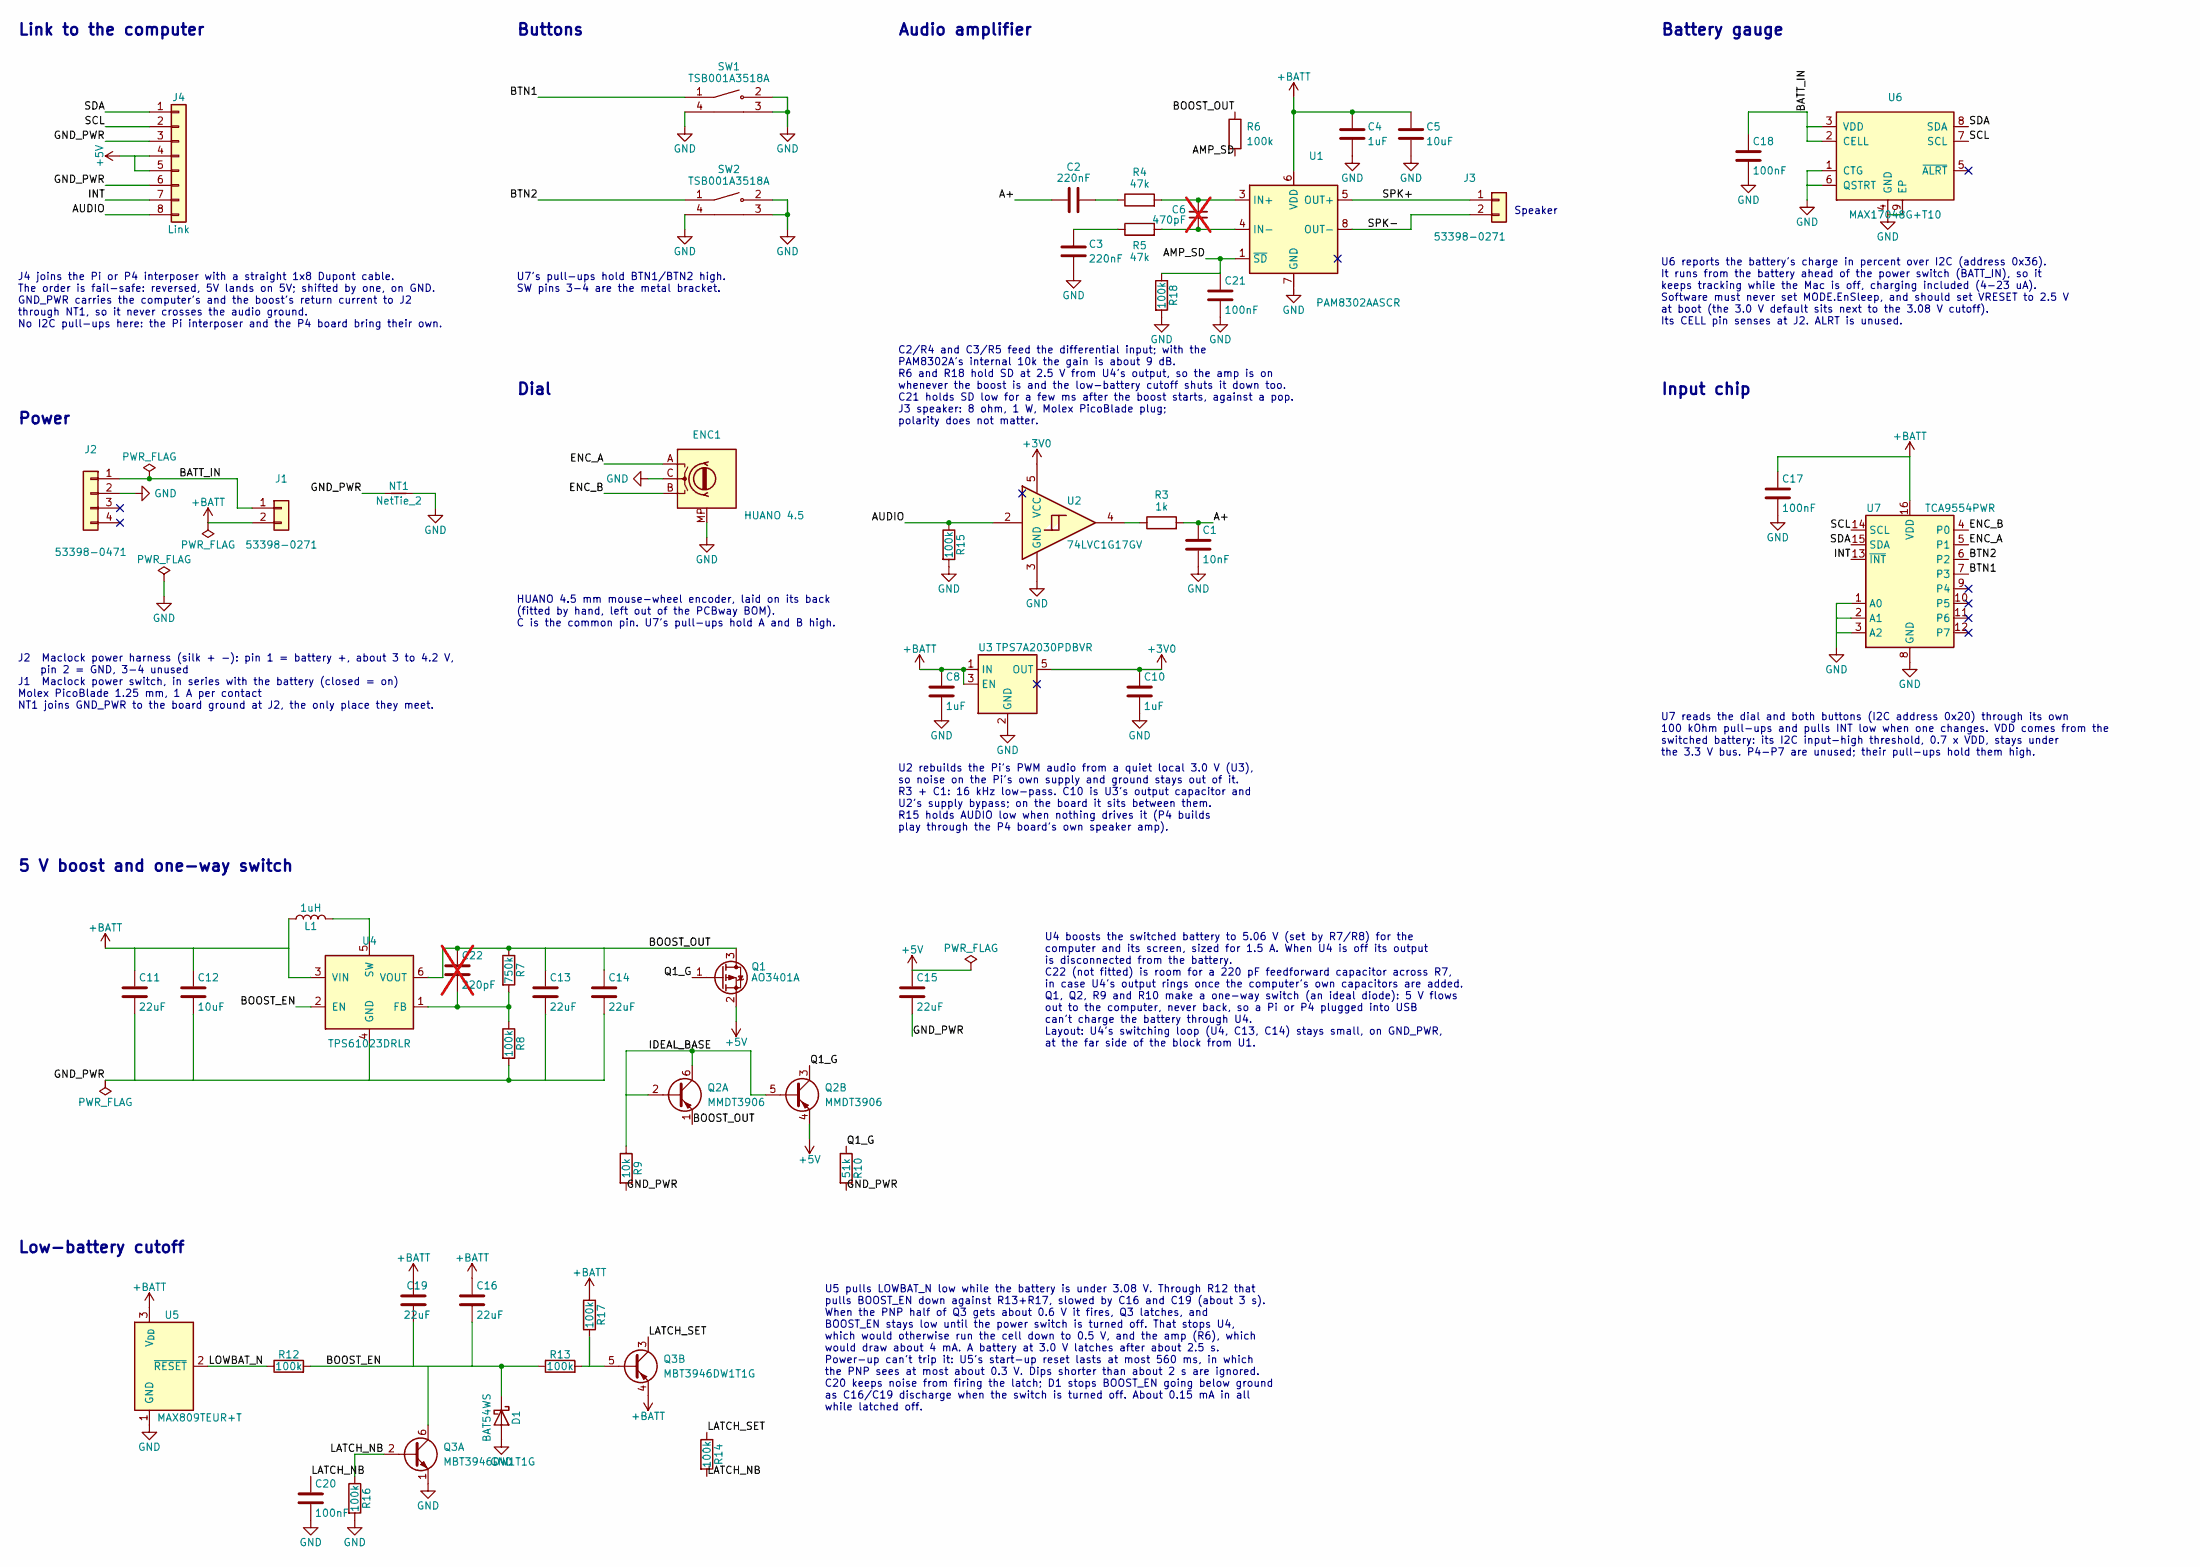
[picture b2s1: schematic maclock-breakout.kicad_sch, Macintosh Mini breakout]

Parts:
C1: 10nF; C_0603_1608Metric; MPN 0603B103K500NT; LCSC C57112
C2, C3: 220nF; C_0603_1608Metric; MPN CL10B224KA8NNNC; LCSC C21120
C4, C8, C10: 1uF; C_0603_1608Metric; MPN CL10A105KB8NNNC; LCSC C15849
C5, C12: 10uF; C_0805_2012Metric; MPN CL21A106KAYNNNE; LCSC C15850
C6: 470pF; C_0402_1005Metric_Pad0.74x0.62mm_HandSolder; MPN CL05C471JB5NNNC; LCSC C307449; not fitted
C11, C13, C14, C15, C16, C19: 22uF; C_0805_2012Metric; MPN CL21A226MAQNNNE; LCSC C45783
C17, C18, C20, C21: 100nF; C_0402_1005Metric_Pad0.74x0.62mm_HandSolder; MPN CL05B104KO5NNNC; LCSC C1525
C22: 220pF; C_0402_1005Metric_Pad0.74x0.62mm_HandSolder; MPN CL05C221JB5NNNC; LCSC C307445; not fitted
D1: BAT54WS; D_SOD-323; MPN BAT54WS-7-F; LCSC C124205
ENC1: HUANO 4.5; RotaryEncoder_HUANO_4.5mm_LayFlat_SMD
J1, J3: 53398-0271; Molex_PicoBlade_53398-0271_1x02-1MP_P1.25mm_Vertical; MPN 53398-0271; LCSC C122410
J2: 53398-0471; Molex_PicoBlade_53398-0471_1x04-1MP_P1.25mm_Vertical; MPN 53398-0471; LCSC C17617036
J4: Link; PinHeader_1x08_P2.54mm_Vertical; MPN PZ254V-11-08P; LCSC C492407
L1: 1uH; L_Murata_DFE322520F; MPN DFE322520F-1R0M=P2; LCSC C5623631
NT1: NetTie_2; NetTie-2_SMD_Pad0.5mm
Q1: AO3401A; SOT-23; MPN AO3401A; LCSC C15127
Q2: MMDT3906; SOT-363_SC-70-6; MPN MMDT3906; LCSC C20534
Q3: MBT3946DW1T1G; SOT-363_SC-70-6; MPN MBT3946DW1T1G; LCSC C28272
R3: 1k; R_0402_1005Metric_Pad0.72x0.64mm_HandSolder; MPN 0402WGF1001TCE; LCSC C11702
R4, R5: 47k; R_0402_1005Metric_Pad0.72x0.64mm_HandSolder; MPN 0402WGF4702TCE; LCSC C25792
R6, R8, R12, R13, R14, R15, R16, R17, R18: 100k; R_0402_1005Metric_Pad0.72x0.64mm_HandSolder; MPN 0402WGF1003TCE; LCSC C25741
R7: 750k; R_0402_1005Metric_Pad0.72x0.64mm_HandSolder; MPN 0402WGF7503TCE; LCSC C122545
R9: 10k; R_0402_1005Metric_Pad0.72x0.64mm_HandSolder; MPN 0402WGF1002TCE; LCSC C25744
R10: 51k; R_0402_1005Metric_Pad0.72x0.64mm_HandSolder; MPN 0402WGF5102TCE; LCSC C25794
SW1, SW2: TSB001A3518A; SW-SMD_TSB001XXXX; MPN TSB001A3518A; LCSC C2888448
U1: PAM8302AASCR; MSOP-8_3x3mm_P0.65mm; MPN PAM8302AASCR; LCSC C113367
U2: 74LVC1G17GV; SOT-23-5; MPN 74LVC1G17GV,125; LCSC C6076
U3: TPS7A2030PDBVR; SOT-23-5; MPN TPS7A2030PDBVR; LCSC C963429
U4: TPS61023DRLR; SOT-563; MPN TPS61023DRLR; LCSC C919459
U5: MAX809TEUR+T; SOT-23; MPN MAX809TEUR+T; LCSC C16711
U6: MAX17048G+T10; TDFN-8-1EP_2x2mm_P0.5mm_EP0.8x1.2mm; MPN MAX17048G+T10; LCSC C2682616
U7: TCA9554PWR; TSSOP-16_4.4x5mm_P0.65mm; MPN TCA9554PWR; LCSC C477924

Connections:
+3V0: C10.1, U2.5 (VCC), U3.5 (OUT)
+5V: C15.1, J4.4, J4.5, Q1.2 (S), Q2.4 (E2)
+BATT: C4.1, C5.1, C8.1, C11.1, C12.1, C16.1, C17.1, C19.1, J1.2, L1.1, Q3.4 (E2), R17.1, U1.6 (VDD), U3.1 (IN), U3.3 (EN), U4.3 (VIN), U5.3 (V_{DD}), U7.16 (VDD)
/A+: C1.1, C2.1, R3.2
/AMP_SD: C21.1, R6.2, R18.1, U1.1 (~SD)
/AUDIO: J4.8, R15.1, U2.2
/BATT_IN: C18.1, J1.1, J2.1, U6.2 (CELL), U6.3 (VDD)
/BOOST_EN: C16.2, C19.2, D1.1 (K), Q3.6 (C1), R12.2, R13.1, U4.2 (EN)
/BOOST_OUT: C13.1, C14.1, C22.1, Q1.3 (D), Q2.1 (E1), R6.1, R7.1, U4.6 (VOUT)
/BTN1: SW1.1, U7.7 (P3)
/BTN2: SW2.1, U7.6 (P2)
/ENC_A: ENC1.A, U7.5 (P1)
/ENC_B: ENC1.B, U7.4 (P0)
/GND_PWR: C11.2, C12.2, C13.2, C14.2, C15.2, J4.3, J4.6, NT1.1, R8.2, R9.2, R10.2, U4.4 (GND)
/IDEAL_BASE: Q2.2 (B1), Q2.5 (B2), Q2.6 (C1), R9.1
/INT: J4.7, U7.13 (~INT)
/LATCH_NB: C20.1, Q3.2 (B1), R14.2, R16.1
/LATCH_SET: Q3.3 (C2), R14.1
/LOWBAT_N: R12.1, U5.2 (~RESET)
/Q1_G: Q1.1 (G), Q2.3 (C2), R10.1
/SCL: J4.2, U6.7 (SCL), U7.14 (SCL)
/SDA: J4.1, U6.8 (SDA), U7.15 (SDA)
/SPK+: J3.1, U1.5 (OUT+)
/SPK-: J3.2, U1.8 (OUT-)
GND: C1.2, C3.1, C4.2, C5.2, C8.2, C10.2, C17.2, C18.2, C20.2, C21.2, D1.2 (A), ENC1.C, ENC1.MP, J2.2, NT1.2, Q3.1 (E1), R15.2, R16.2, R18.2, SW1.2, SW1.3, SW1.4, SW2.2, SW2.3, SW2.4, U1.7 (GND), U2.3 (GND), U3.2 (GND), U5.1 (GND), U6.1 (CTG), U6.4 (GND), U6.6 (QSTRT), U6.9 (EP), U7.1 (A0), U7.2 (A1), U7.3 (A2), U7.8 (GND)
unnamed: C2.2, R4.1
unnamed: C3.2, R5.1
unnamed: Q3.5 (B2), R13.2, R17.2
unnamed: R3.1, U2.4
unnamed: C6.1, R4.2, U1.3 (IN+)
unnamed: C6.2, R5.2, U1.4 (IN-)
unnamed: C22.2, R7.2, R8.1, U4.1 (FB)
unnamed: L1.2, U4.5 (SW)

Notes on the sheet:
Dial
Low-battery cutoff
HUANO 4.5 mm mouse-wheel encoder, laid on its back (fitted by hand, left out of the PCBway BOM). C is the common pin. U7's pull-ups hold A and B high.
Link to the computer
Power
J4 joins the Pi or P4 interposer with a straight 1x8 Dupont cable. The order is fail-safe: reversed, 5V lands on 5V; shifted by one, on GND. GND_PWR carries the computer's and the boost's return current to J2 through NT1, so it never crosses the audio ground. No I2C pull-ups here: the Pi interposer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
Speaker
U2 rebuilds the Pi's PWM audio from a quiet local 3.0 V (U3), so noise on the Pi's own supply and ground stays out of it. R3 + C1: 16 kHz low-pass. C10 is U3's output capacitor and U2's supply bypass; on the board it sits between them. R15 holds AUDIO low when nothing drives it (P4 builds play thro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
J2 Maclock power harness (silk + -): pin 1 = battery +, about 3 to 4.2 V, pin 2 = GND, 3-4 unused J1 Maclock power switch, in series with the battery (closed = on) Molex PicoBlade 1.25 mm, 1 A per contact NT1 joins GND_PWR to the board ground at J2, the only place they meet.
U6 reports the battery's charge in percent over I2C (address 0x36). It runs from the battery ahead of the power switch (BATT_IN), so it keeps tracking while the Mac is off, charging included (4-23 uA). Software must never set MODE.EnSleep, and should set VRESET to 2.5 V at boot (the 3.0 V default s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
U7's pull-ups hold BTN1/BTN2 high. SW pins 3-4 are the metal bracket.
Buttons
Input chip
U4 boosts the switched battery to 5.06 V (set by R7/R8) for the computer and its screen, sized for 1.5 A. When U4 is off its output is disconnected from the battery. C22 (not fitted) is room for a 220 pF feedforward capacitor across R7, in case U4's output rings once the computer's own capacitors a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
U7 reads the dial and both buttons (I2C address 0x20) through its own 100 kOhm pull-ups and pulls INT low when one changes. VDD comes from the switched battery: its I2C input-high threshold, 0.7 x VDD, stays under the 3.3 V bus. P4-P7 are unused; their pull-ups hold them high.
Battery gauge
Audio amplifier
U5 pulls LOWBAT_N low while the battery is under 3.08 V. Through R12 that pulls BOOST_EN down against R13+R17, slowed by C16 and C19 (about 3 s). When the PNP half of Q3 gets about 0.6 V it fires, Q3 latches, and BOOST_EN stays low until the power switch is turned off. That stops U4, which would ot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
5 V boost and one-way switch
C2/R4 and C3/R5 feed the differential input; with the PAM8302A's internal 10k the gain is about 9 dB. R6 and R18 hold SD at 2.5 V from U4's output, so the amp is on whenever the boost is and the low-battery cutoff shuts it down too. C21 holds SD low for a few ms after the boost starts, against a po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

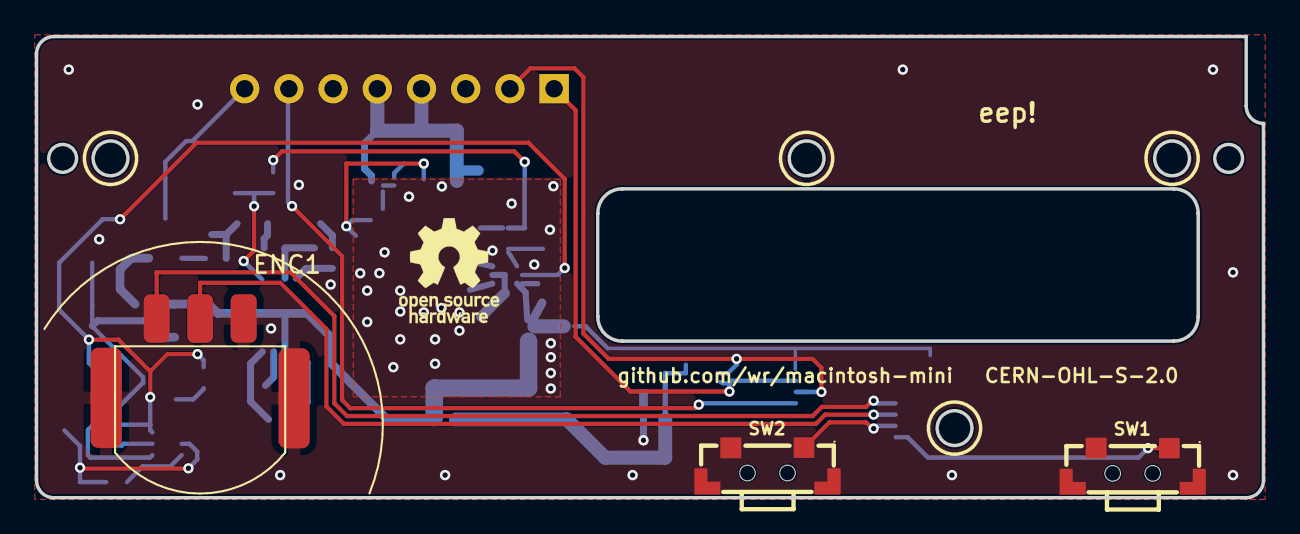
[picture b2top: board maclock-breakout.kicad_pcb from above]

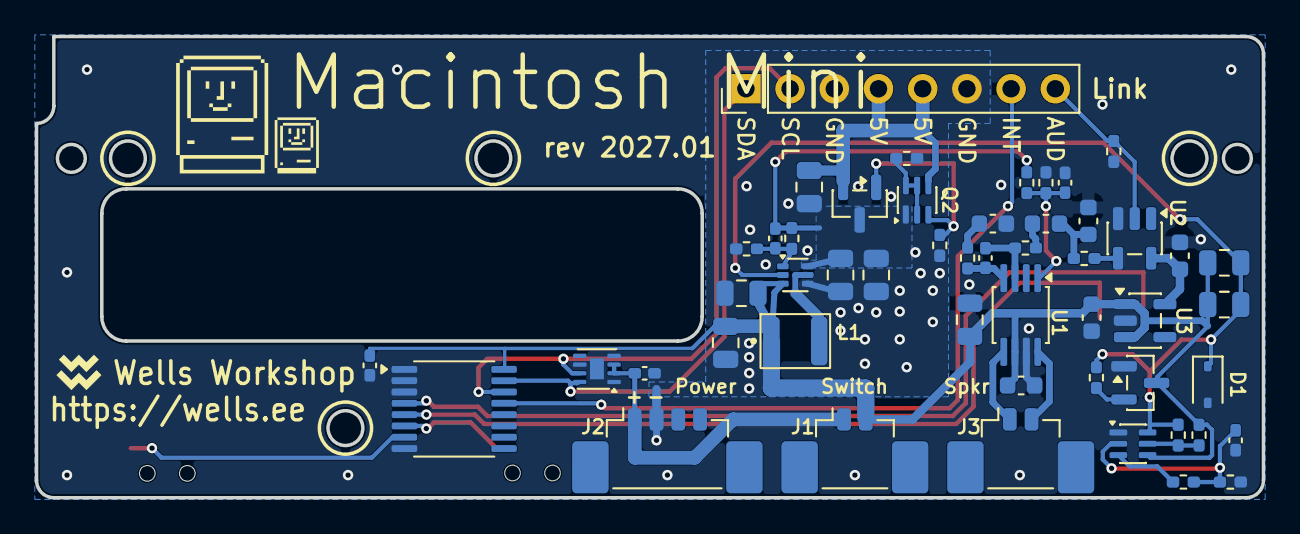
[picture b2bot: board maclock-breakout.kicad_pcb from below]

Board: 2 copper layers, 70.5 x 26.5 mm, 56 parts (52 on the bottom side), 33 nets.

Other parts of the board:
LOGO1: OSHW-Logo_5.7x6mm_SilkScreen

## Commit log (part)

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2026-05-14 updated board design to 2026.5
2026-05-28 Add BasiliskII (68k) install path for leaner emulation on Pi Zero 2 W
    SheepShaver interprets PowerPC on the Zero 2 W's Cortex-A53 (its JIT is
    x86-only), which is the worst case for this hardware. Emulating a 68k Mac
    (System 7) via BasiliskII is far cheaper to interpret, so add it as a
    parallel install path and make it the default in the menu, keeping
    SheepShaver selectable for PPC-era software.
    Tuning follows the proven MacintoshPi-on-Zero-2-W config: frameskip 2,
2026-05-28 BasiliskII: add --rom flag, libmpfr-dev dep, autostart switching, debug-exit fix
    Shaken out by an end-to-end install on the actual Pi Zero 2 W:
    - --rom <file>: a Pi may already hold a 4 MB PPC ROM named "ROM"; the 68k
    ROM needs explicit selection (the default "ROM" would be the wrong one).
    - libmpfr-dev: BasiliskII's FPU core compiles with -DFPU_MPFR and won't
    build on a fresh Pi without the MPFR headers.
    - Each emulator's profile patch now strips the other's autostart block, so
2026-05-28 Add kiosk lifecycle controls; make re-runs update/switch-safe
    - Reset button double-press force-quits the emulator to a Pi prompt;
    button_handler gains debounce-aware single vs double dispatch.
    - Launcher keys off the emulator's exit status: 0 (Mac "Shut Down") or
    143 (double-reset) drop to a Pi prompt, anything else relaunches.
    Mac "Restart" reboots the VM in place, so it auto-reboots for free.
    - Add a `macintosh` command to (re)boot the Mac from a shell.
2026-05-28 Enable VOSF for BasiliskII
    VOSF re-blits only changed screen regions instead of the whole frame
    every tick — noticeably snappier UI. Verified stable on the Pi Zero 2 W
    (aarch64), so drop the old --disable-vosf workaround.
    Refs: W-247
2026-05-28 Add boot preflight for missing/unconfigured ROM or disk
    New /usr/local/bin/mac-preflight runs before the emulator: if the
    configured ROM+disk are present it boots; if not, it auto-fills the
    prefs when exactly one ROM (matched by size) and one disk image exist
    in $HOME; otherwise it prints what's missing/ambiguous and drops to a
    prompt instead of failing cryptically. Wired into both launchers.
    Refs: W-247, W-266
2026-05-28 README: list which disk image formats work
    Most people grab an image online; spell out what mounts (raw hard-disk
    images, any extension; sparsebundle) and what doesn't (.dmg/.smi/.toast,
    still-zipped files).
    Refs: W-247
2026-05-28 Reorganize emulator guides into emulators/; default networking
    - Move the manual guides into emulators/ (SheepShaver.md, BasiliskII.md)
    next to the shared chimes/, with an index README. Adds a BasiliskII
    manual guide that was missing.
    - Add `ether slirp` to both prefs so networking works out of the box.
    - Accuracy + path fixes across all READMEs (BasiliskII is the default,
    button single/double behavior, disk formats, updated cross-links and
2026-05-28 Tidy manual-install wording in READMEs
    Bullet the root README's manual-install guide links and trim the
    maclock-build emulator paragraph.
    Refs: W-247
2026-05-28 Stop tracking KiCad fp-lib-table
    It pinned KiCad to a machine-specific absolute path. Remove it and
    gitignore the project-local KiCad lib tables.
2026-05-28 Add BasiliskII (68k) emulator as default
    * Add BasiliskII (68k) install path for leaner emulation on Pi Zero 2 W
    SheepShaver interprets PowerPC on the Zero 2 W's Cortex-A53 (its JIT is
    x86-only), which is the worst case for this hardware. Emulating a 68k Mac
    (System 7) via BasiliskII is far cheaper to interpret, so add it as a
    parallel install path and make it the default in the menu, keeping
    SheepShaver selectable for PPC-era software.
2026-05-28 setup: clearer install menu
    Replace the cryptic "Both" default with self-describing options, a blank
    separator after the recommended choice, and widen the menu box to fit.
    Refs: W-269
2026-05-28 docs: write the product name as "Basilisk II" (with a space)
    Apply the spaced name in user-facing prose and the install-menu labels.
    The binary, paths, commands, and the BasiliskII.md filename/links are
    left as-is.
    Refs: W-269
2026-05-28 setup: reconfigure menu for existing installs
    When prefs already exist for the chosen emulator, offer a keep-or-change
    menu (disk image, startup chime, color depth) instead of silently keeping
    everything. Changes are applied in place; fresh-install flow unchanged.
    Refs: W-270
2026-05-28 setup: polish installer and settings menus
    - Install menu: title "Macintosh Mini Installer", no prompt line, no
    blank separator, shorter labels.
    - Emulator Settings: drop the "Keep" row; OK=<Change> the highlighted
    setting, Cancel=<Continue> to proceed; show current values; title
    "Emulator Settings". Persist the chosen chime so its value can show.
    - Shorten the performance prompt text.
2026-05-28 setup: colons + full labels in settings, clearer perf prompt
    Emulator Settings rows read "Disk image:/Startup chime:/Color depth:"
    with full color-depth text (e.g. "Black & White 1-bit"). Performance
    prompt retitled, prompt line dropped, options described plainly.
    Refs: W-269, W-270
2026-05-29 Clearer installer menu (#8)
    * setup: clearer install menu
    Replace the cryptic "Both" default with self-describing options, a blank
    separator after the recommended choice, and widen the menu box to fit.
    Refs: W-269
    * docs: write the product name as "Basilisk II" (with a space)
    Apply the spaced name in user-facing prose and the install-menu labels.
2026-05-29 setup: suppress emulator core dumps; check SheepShaver ROM size
    - ulimit -c 0 in both launchers — the reset button stops getty/cage out
    from under the emulator, which faults on teardown and dropped a 31 MB
    core in $HOME each press. Crash->relaunch still works; just no junk.
    - check_sheepshaver_assets now rejects a 512 KB/1 MB 68k ROM (needs the
    4 MB PowerPC ROM), mirroring the existing BasiliskII ROM check.
    Refs: W-271
2026-05-29 setup: suppress emulator core dumps; check SheepShaver ROM size (#9)
    - ulimit -c 0 in both launchers — the reset button stops getty/cage out
    from under the emulator, which faults on teardown and dropped a 31 MB
    core in $HOME each press. Crash->relaunch still works; just no junk.
    - check_sheepshaver_assets now rejects a 512 KB/1 MB 68k ROM (needs the
    4 MB PowerPC ROM), mirroring the existing BasiliskII ROM check.
    Refs: W-271
2026-05-29 setup: version the installer
    Add a VERSION constant (1.0.0) and surface it at startup — in the banner
    and the install-menu title ("Macintosh Mini Installer v1.0.0").
    Refs: W-272
2026-05-29 setup: version the installer (#10)
    Add a VERSION constant (1.0.0) and surface it at startup — in the banner
    and the install-menu title ("Macintosh Mini Installer v1.0.0").
    Refs: W-272
2026-06-01 Add pantry quick-reorder terminal (ESP32-S3 + LVGL touchscreen)
    A pantry touchscreen where tapping a product tile adds the item directly
    to your Amazon cart. Runs entirely on an ESP32-S3 with an LVGL display
    (default target: Elecrow ESP32-S3 3.5" Terminal) — no backend.
    Since Amazon has no consumer ordering API, the device authenticates as
    you by replaying stored session cookies against the add-to-cart endpoint,
    then you finish checkout from the Amazon app. Secrets (Wi-Fi + cookies)
2026-06-09 setup: prompt for BasiliskII modelid (5 vs 14); bump to 1.1.0
    System 7.5 and Mac OS 8 require modelid 14 (Quadra); 7.0/7.1 needs
    modelid 5 (Mac IIci). Previously hardcoded to 5, which sad-Macs on 7.5+.
    Adds a menu prompt during fresh installs and a "Mac model" row in the
    reconfigure menu for existing installs, plus a --modelid flag.

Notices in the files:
maclock-pcb/README.md:
CERN-OHL-S-2.0 — see [`LICENSE`](./LICENSE). You can make, modify and sell the board. Boards you make must point to their source, and a modified design must be published under the same licence.
maclock-interposer/maclock-interposer.kicad_pcb:
github.com/wr/macintosh-mini CERN-OHL-S-2.0
maclock-pcb/maclock-breakout.kicad_pcb:
Licensed CERN-OHL-S-2.0
